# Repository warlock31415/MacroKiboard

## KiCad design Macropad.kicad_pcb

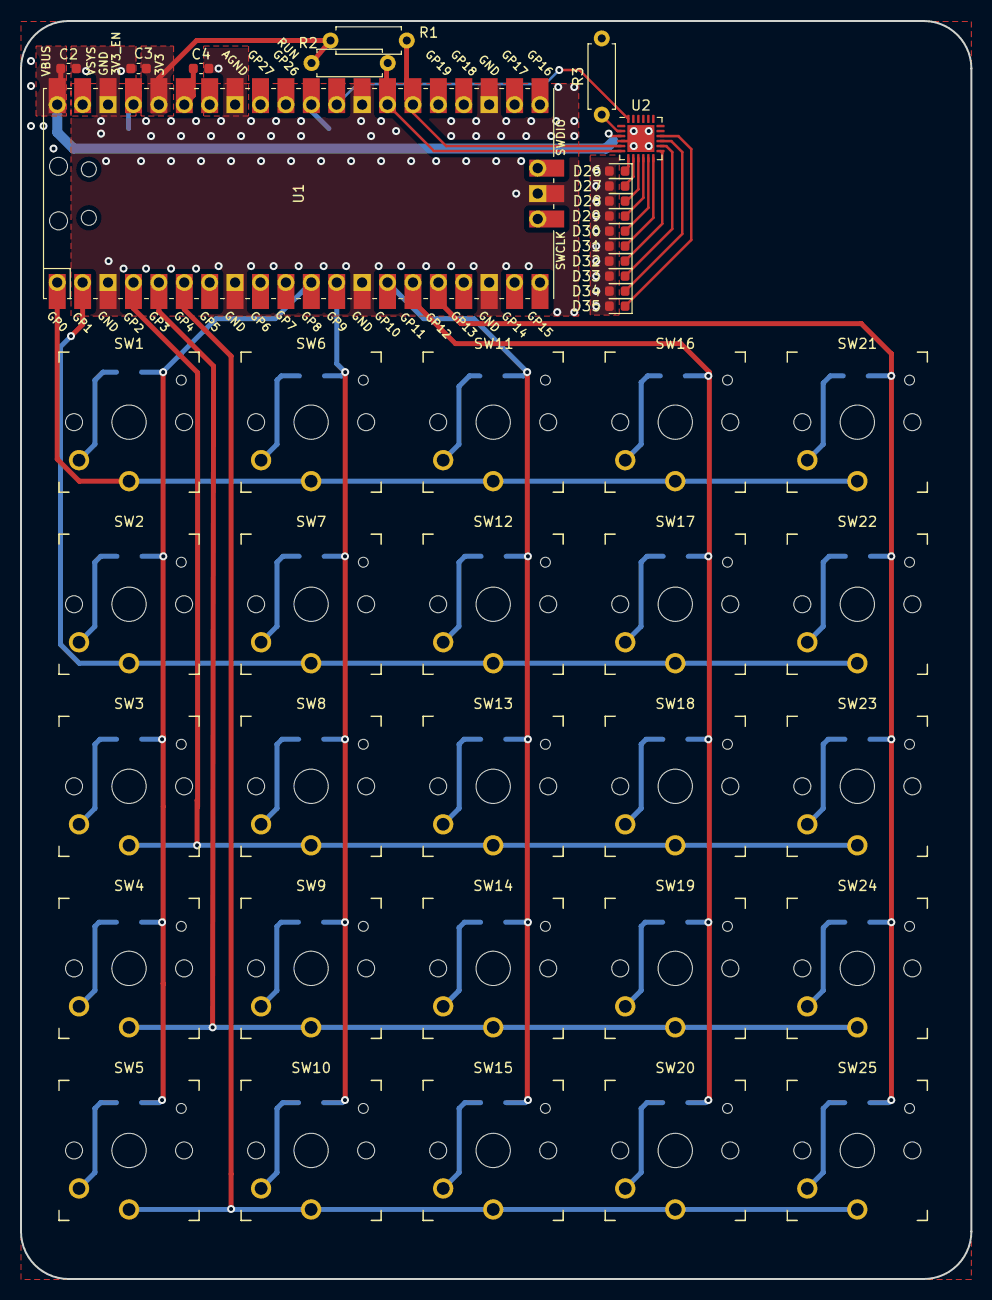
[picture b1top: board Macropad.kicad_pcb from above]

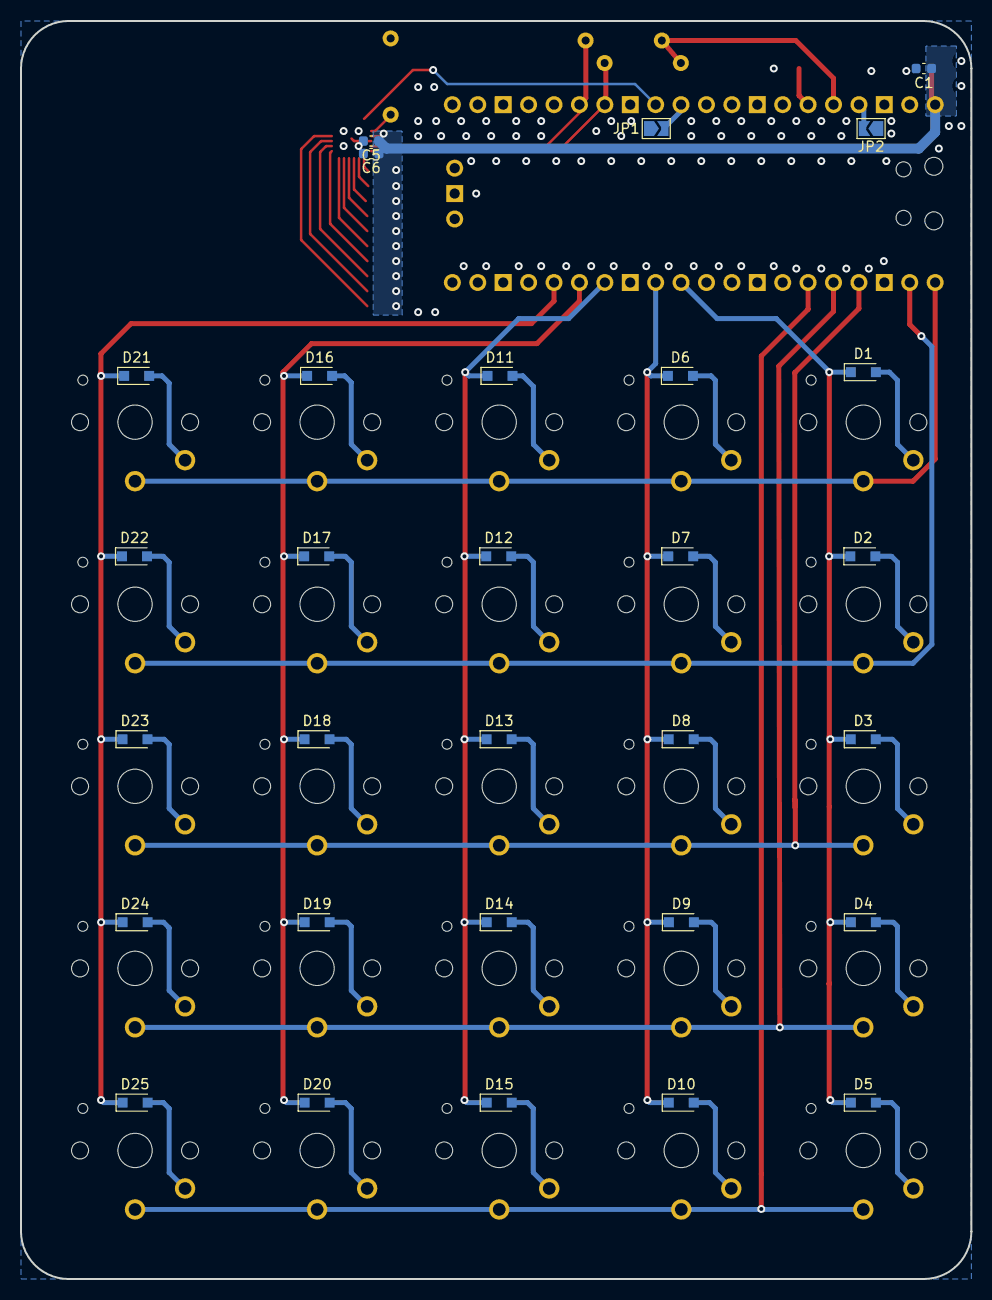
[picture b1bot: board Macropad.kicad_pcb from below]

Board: 2 copper layers, 95.0 x 125.7 mm, 73 parts (30 on the bottom side), 55 nets.

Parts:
C1, C5: 0.1u; C_0603_1608Metric
C2, C3, C4, C6: 1u; C_0603_1608Metric
D1, D2, D3, D4, D5, D6, D7, D8, D9, D10, D11, D12, D13, D14, D15, D16, D17, D18, D19, D20, D21, D22, D23, D24, D25: D_Small; D_SOD-323_HandSoldering
D26, D27, D28, D29, D30, D31, D32, D33, D34, D35: LED_Small; LED_0603_1608Metric
JP1, JP2: Jumper_2_Open; SolderJumper-2_P1.3mm_Open_TrianglePad1.0x1.5mm
R1, R2, R3: 4.7k; R_Axial_DIN0207_L6.3mm_D2.5mm_P7.62mm_Horizontal
SW1, SW2, SW3, SW4, SW5, SW6, SW7, SW8, SW9, SW10, SW11, SW12, SW13, SW14, SW15, SW16, SW17, SW18, SW19, SW20, SW21, SW22, SW23, SW24, SW25: SW_DIP_x01; SW_PG1350
U1: Pico; RPi_Pico_SMD_TH
U2: IS31FL3218-QF; QFN-24-1EP_4x4mm_P0.5mm_EP2.7x2.7mm

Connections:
+3V3: C3.1, R1.1, R2.1, U1.36 (3V3)
/Key Matrix/COL1: D1.1 (K), D2.1 (K), D3.1 (K), D4.1 (K), D5.1 (K), U1.11 (GPIO8)
/Key Matrix/COL2: D6.1 (K), D7.1 (K), D8.1 (K), D9.1 (K), D10.1 (K), U1.12 (GPIO9)
/Key Matrix/COL3: D11.1 (K), D12.1 (K), D13.1 (K), D14.1 (K), D15.1 (K), U1.14 (GPIO10)
/Key Matrix/COL4: D16.1 (K), D17.1 (K), D18.1 (K), D19.1 (K), D20.1 (K), U1.15 (GPIO11)
/Key Matrix/COL5: D21.1 (K), D22.1 (K), D23.1 (K), D24.1 (K), D25.1 (K), U1.16 (GPIO12)
/Key Matrix/ROW1: SW1.1, SW6.1, SW11.1, SW16.1, SW21.1, U1.1 (GPIO0)
/Key Matrix/ROW2: SW2.1, SW7.1, SW12.1, SW17.1, SW22.1, U1.2 (GPIO1)
/Key Matrix/ROW3: SW3.1, SW8.1, SW13.1, SW18.1, SW23.1, U1.4 (GPIO2)
/Key Matrix/ROW4: SW4.1, SW9.1, SW14.1, SW19.1, SW24.1, U1.5 (GPIO3)
/Key Matrix/ROW5: SW5.1, SW10.1, SW15.1, SW20.1, SW25.1, U1.6 (GPIO4)
/LED Matrix/I2C1.SCL: R2.2, U1.27 (GPIO21), U2.6 (SCL)
/LED Matrix/I2C1.SDA: R1.2, U1.26 (GPIO20), U2.5 (SDA)
/LED Matrix/~SDB: U1.29 (GPIO22), U2.24 (~SDB)
GND: C1.2, C2.2, C3.2, C4.2, C5.2, C6.2, JP1.1 (A), JP2.1 (A), R3.2, U1.3 (GND), U1.8 (GND), U1.13 (GND), U1.18 (GND), U1.23 (GND), U1.28 (GND), U1.33 (AGND), U1.38 (GND), U1.42 (GND), U2.4 (GND), U2.25 (GND)
unnamed: C4.1, U1.35 (ADC_VREF)
unnamed: D1.2 (A), SW1.2
unnamed: D2.2 (A), SW2.2
unnamed: D3.2 (A), SW3.2
unnamed: D4.2 (A), SW4.2
unnamed: D5.2 (A), SW5.2
unnamed: D6.2 (A), SW6.2
unnamed: D7.2 (A), SW7.2
unnamed: D8.2 (A), SW8.2
unnamed: D9.2 (A), SW9.2
unnamed: D10.2 (A), SW10.2
unnamed: D11.2 (A), SW11.2
unnamed: D12.2 (A), SW12.2
unnamed: D13.2 (A), SW13.2
unnamed: D14.2 (A), SW14.2
unnamed: D15.2 (A), SW15.2
unnamed: D16.2 (A), SW16.2
unnamed: D17.2 (A), SW17.2
unnamed: D18.2 (A), SW18.2
unnamed: D19.2 (A), SW19.2
unnamed: D20.2 (A), SW20.2
unnamed: D21.2 (A), SW21.2
unnamed: D22.2 (A), SW22.2
unnamed: D23.2 (A), SW23.2
unnamed: D24.2 (A), SW24.2
unnamed: D25.2 (A), SW25.2
unnamed: D26.1 (K), U2.7 (OUT1)
unnamed: D27.1 (K), U2.8 (OUT2)
unnamed: D28.1 (K), U2.9 (OUT3)
unnamed: D29.1 (K), U2.10 (OUT4)
unnamed: D30.1 (K), U2.11 (OUT5)
unnamed: D31.1 (K), U2.12 (OUT6)
unnamed: D32.1 (K), U2.13 (OUT7)
unnamed: D33.1 (K), U2.14 (OUT8)
unnamed: D34.1 (K), U2.15 (OUT9)
unnamed: D35.1 (K), U2.16 (OUT10)
unnamed: JP1.2 (B), U1.30 (RUN)
unnamed: JP2.2 (B), U1.37 (3V3_EN)
unnamed: R3.1, U2.2 (R_EXT)
VBUS: C1.1, C2.1, C5.1, C6.1, D26.2 (A), D27.2 (A), D28.2 (A), D29.2 (A), D30.2 (A), D31.2 (A), D32.2 (A), D33.2 (A), D34.2 (A), D35.2 (A), U1.40 (VBUS), U2.3 (VCC)

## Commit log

2022-04-29 Moving files from gitlab
2022-07-26 Adding ledDriver library
2023-04-19 Trackball now shows status of the caps lock
2023-04-19 Fixed an error from the last commit
